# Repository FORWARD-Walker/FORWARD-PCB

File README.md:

MAIN contains ESP-32D Wroom, sensors, and connectors to other boards.
POWER contains voltage regulators and connection for AA battery pack.

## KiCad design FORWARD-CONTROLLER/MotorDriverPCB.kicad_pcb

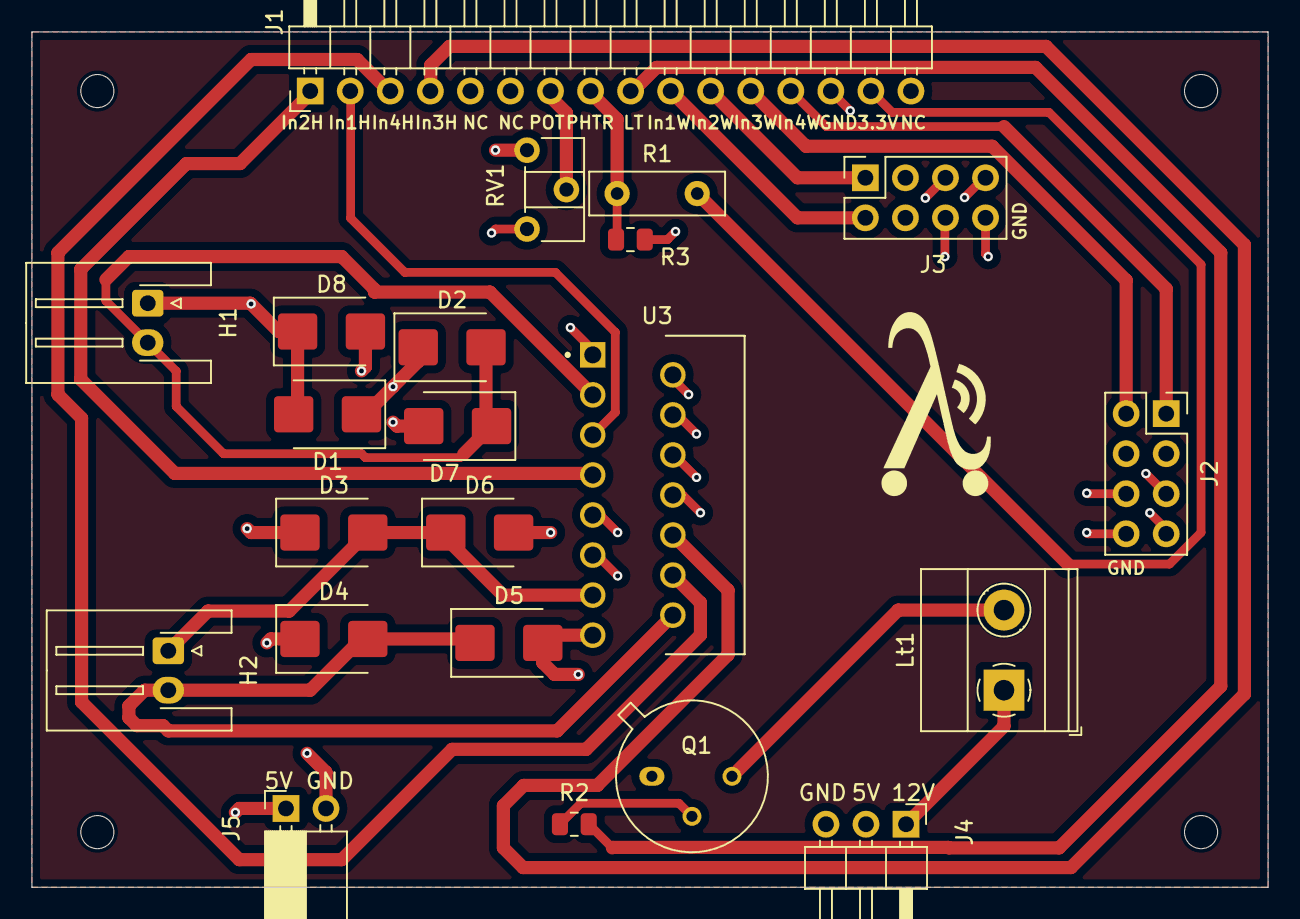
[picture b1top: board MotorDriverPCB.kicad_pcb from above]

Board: 4 copper layers, 78.4 x 54.2 mm, 22 parts (0 on the bottom side), 21 nets.

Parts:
D1, D2, D3, D4, D5, D6, D7, D8: STTH212U; D_SMB
H1, H2: Screw_Terminal_01x02; JST_XH_S2B-XH-A-1_1x02_P2.50mm_Horizontal
J1: Conn_01x16_Pin; PinHeader_1x16_P2.54mm_Horizontal
J2, J3: Conn_02x04_Counter_Clockwise; PinSocket_2x04_P2.54mm_Vertical
J4: Conn_01x03_Socket; PinHeader_1x03_P2.54mm_Horizontal
J5: Conn_01x02_Socket; PinSocket_1x02_P2.54mm_Horizontal
Lt1: Screw_Terminal_01x02; TerminalBlock_Phoenix_MKDS-1,5-2-5.08_1x02_P5.08mm_Horizont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
Q1: 2N2219; TO-39-3
R1: R_Photo; R_Box_L8.4mm_W2.5mm_P5.08mm
R2: 1k; R_0805_2012Metric
R3: 10k; R_0805_2012Metric
RV1: R_Potentiometer; Potentiometer_ACP_CA6-H2,5_Horizontal
U3: L298N; TO127P2020X500X2100-15

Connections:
+3.3V: J1.15, R1.2
+5V: D1.1 (K), D2.1 (K), D3.1 (K), D4.1 (K), J2.5, J2.6, J2.7, J3.5, J3.6, J3.7, J4.2, J5.1, RV1.1, U3.4 (VS), U3.6 (ENA), U3.9 (VSS), U3.11 (ENB)
+12V: J4.1, Lt1.1
GND: D5.2 (A), D6.2 (A), D7.2 (A), D8.2 (A), J1.14, J2.8, J3.8, J4.3, J5.2, Q1.1 (E), R3.2, RV1.3, U3.1 (SENSE_A), U3.8 (GND), U3.15 (SENSE_B)
IN1U2: J1.10, J3.2
IN1U3: J1.2, U3.5 (IN1)
IN2U2: J1.11, J3.1
IN2U3: J1.1, U3.7 (IN2)
IN3U2: J1.12, J2.2
IN3U3: J1.4, U3.10 (IN3)
IN4U2: J1.13, J2.1
IN4U3: J1.3, U3.12 (IN4)
LIGHT: J1.9, R2.2
NPN: Lt1.2, Q1.3 (C)
unnamed: Q1.2 (B), R2.1
OUT1U3: D1.2 (A), D8.1 (K), H1.1, U3.2 (OUT1)
OUT2U3: D2.2 (A), D7.1 (K), H1.2, U3.3 (OUT2)
OUT3U3: D3.2 (A), D6.1 (K), H2.1, U3.13 (OUT3)
OUT4U3: D4.2 (A), D5.1 (K), H2.2, U3.14 (OUT4)
PHOTO: J1.8, R1.1, R3.1
POW: J1.7, RV1.2

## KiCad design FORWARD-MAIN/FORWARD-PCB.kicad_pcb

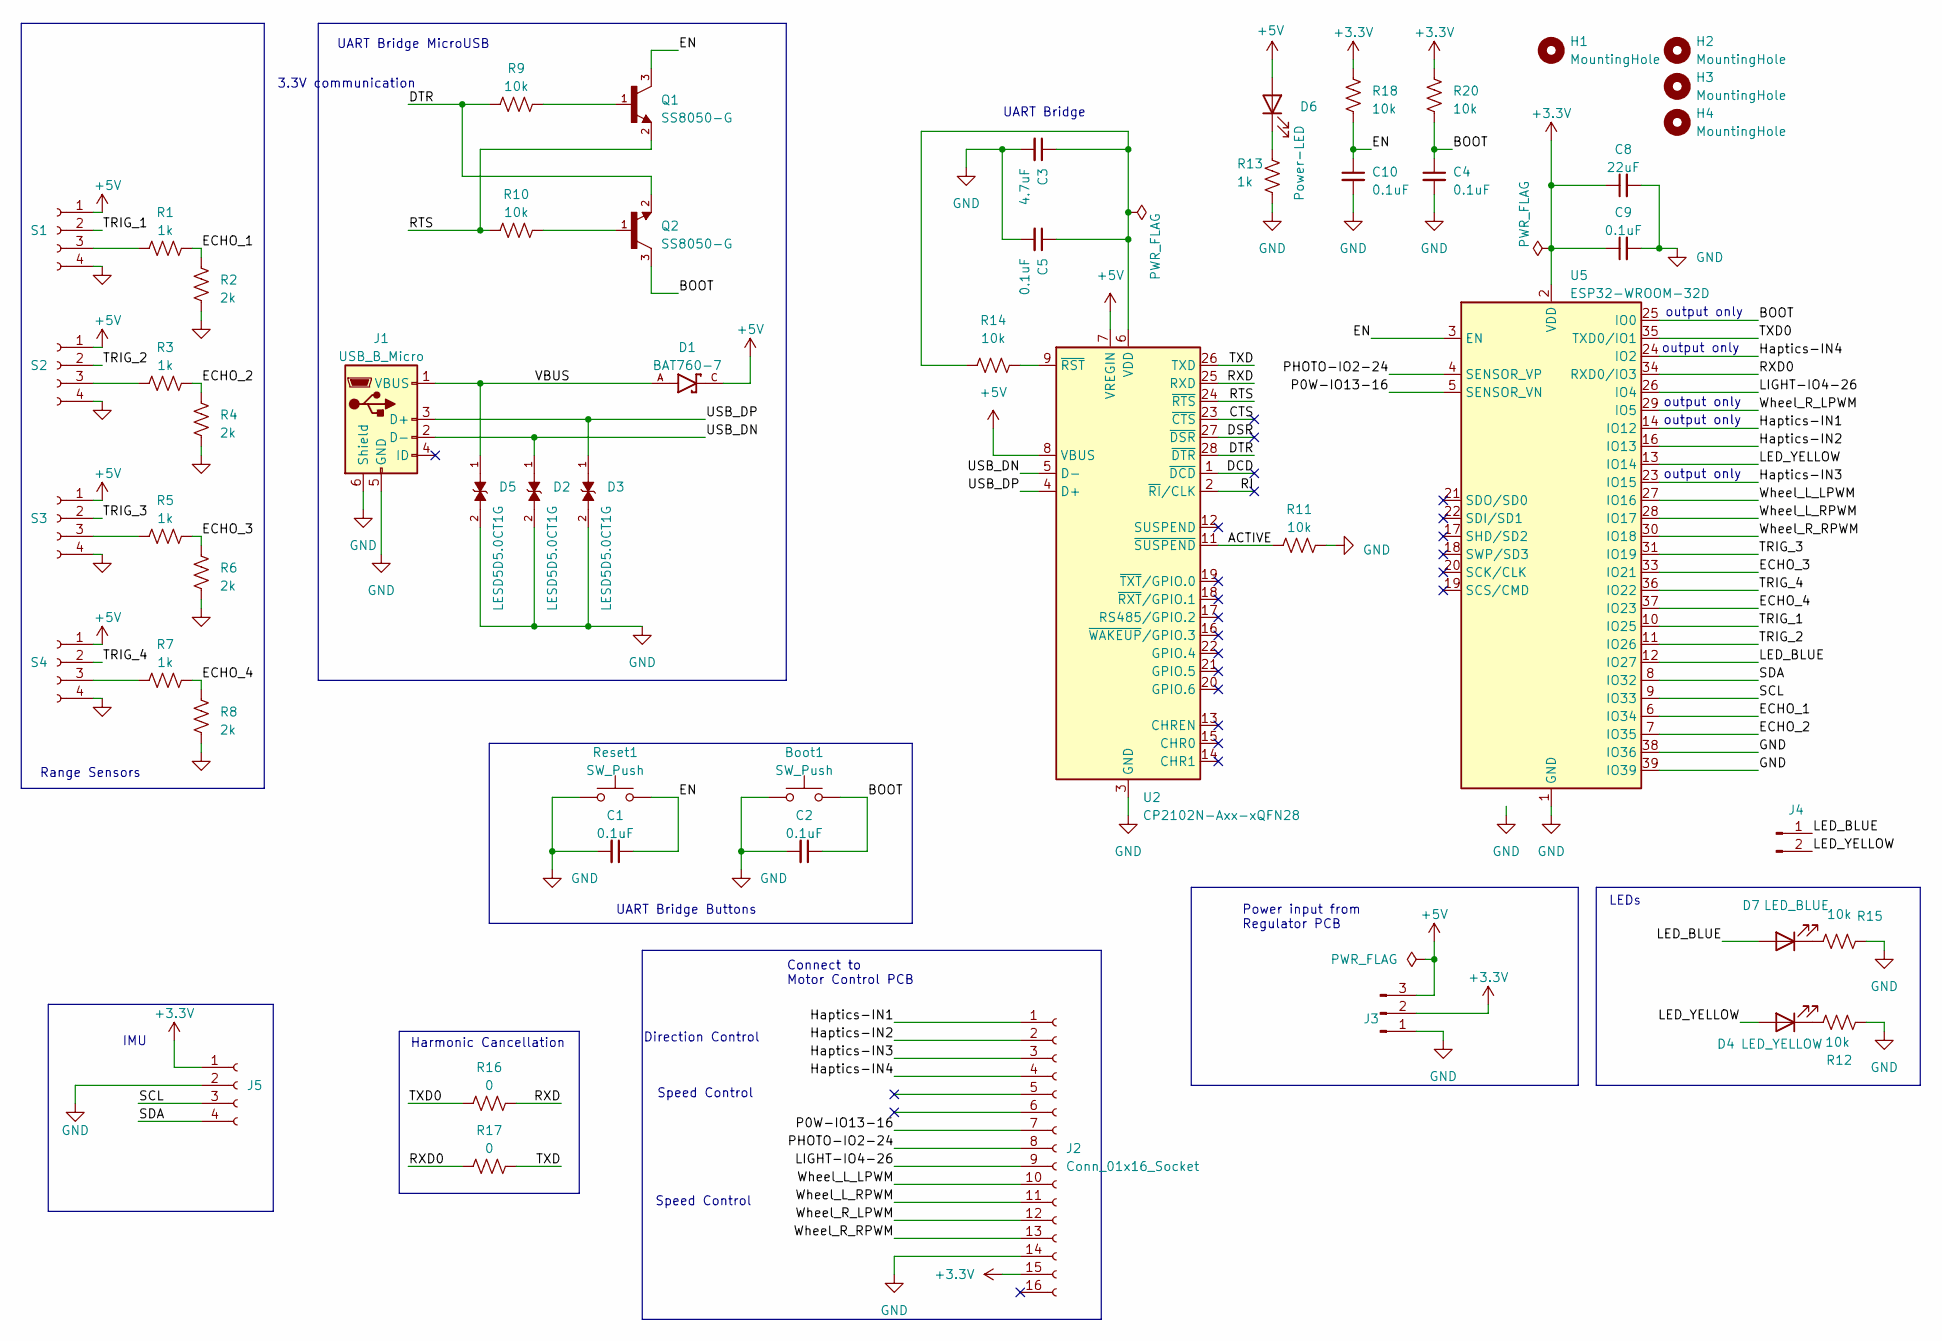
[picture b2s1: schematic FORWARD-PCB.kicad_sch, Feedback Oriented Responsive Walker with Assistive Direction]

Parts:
Boot1: SW_Push; SW_SPST_TL3305A
C1, C2, C4, C5, C9, C10: 0.1uF; C_0805_2012Metric
C3: 4.7uF; C_0805_2012Metric
C8: 22uF; C_0805_2012Metric
D1: BAT760-7; SOD2513X120N; PARTREV 9-2
D2, D3, D5: LESD5D5.0CT1G; TVS_LESD5D5.0CT1G; PARTREV O
D4: LED_YELLOW; LED_0805_2012Metric
D6: Power-LED; LED_0805_2012Metric
D7: LED_BLUE; LED_0805_2012Metric
H1, H2, H3, H4: MountingHole; MountingHole_2.2mm_M2
J1: USB_B_Micro; USB_Micro-B_Wuerth_629105150521
J2: Conn_01x16_Socket; PinSocket_1x16_P2.54mm_Horizontal
J3: Conn_01x03_Pin; JST_XH_S3B-XH-A_1x03_P2.50mm_Horizontal
J4: Conn_01x02_Pin; PinSocket_1x02_P2.54mm_Horizontal
J5: Conn_01x04_Socket; PinSocket_1x04_P2.54mm_Vertical
Q1, Q2: SS8050-G; TRANS_SS8050-G; PARTREV A
R1, R3, R5, R7, R13: 1k; R_0805_2012Metric
R2, R4, R6, R8: 2k; R_0805_2012Metric
R9, R10, R11, R12, R14, R15, R18, R20: 10k; R_0805_2012Metric
R16, R17: 0; R_0805_2012Metric
Reset1: SW_Push; SW_SPST_TL3305A
S1, S2, S3, S4: Conn_01x04_Socket; JST_XH_S4B-XH-A_1x04_P2.50mm_Horizontal
U2: CP2102N-Axx-xQFN28; QFN-28-1EP_5x5mm_P0.5mm_EP3.35x3.35mm
U5: ESP32-WROOM-32D

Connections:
+3.3V: C8.1, C9.1, J2.15, J3.2, J5.1, R18.1, R20.1, U5.2 (VDD)
+5V: D1.C, D6.2 (A), J3.3, S1.1, S2.1, S3.1, S4.1, U2.7 (VREGIN), U2.8 (VBUS)
/ACTIVE: R11.1, U2.11 (~SUSPEND)
/BOOT: Boot1.2, C2.1, C4.1, Q2.3, R20.2, U5.25 (IO0)
/CTS: U2.23 (~CTS)
/DCD: U2.1 (~DCD)
/DSR: U2.27 (~DSR)
/DTR: Q2.2, R9.1, U2.28 (~DTR)
/ECHO_1: R1.2, R2.1, U5.6 (IO34)
/ECHO_2: R3.2, R4.1, U5.7 (IO35)
/ECHO_3: R5.2, R6.1, U5.33 (IO21)
/ECHO_4: R7.2, R8.1, U5.37 (IO23)
/EN: C1.1, C10.1, Q1.3, R18.2, Reset1.2, U5.3 (EN)
/Haptics-IN1: J2.1, U5.14 (IO12)
/Haptics-IN2: J2.2, U5.16 (IO13)
/Haptics-IN3: J2.3, U5.23 (IO15)
/Haptics-IN4: J2.4, U5.24 (IO2)
/LED_BLUE: D7.2 (A), J4.1, U5.12 (IO27)
/LED_YELLOW: D4.2 (A), J4.2, U5.13 (IO14)
/LIGHT-IO4-26: J2.9, U5.26 (IO4)
/P0W-IO13-16: J2.7, U5.5 (SENSOR_VN)
/PHOTO-IO2-24: J2.8, U5.4 (SENSOR_VP)
/RI: U2.2 (~RI/CLK)
/RTS: Q1.2, R10.1, U2.24 (~RTS)
/RXD: R16.2, U2.25 (RXD)
/RXD0: R17.1, U5.34 (RXD0/IO3)
/SCL: J5.3, U5.9 (IO33)
/SDA: J5.4, U5.8 (IO32)
/TRIG_1: S1.2, U5.10 (IO25)
/TRIG_2: S2.2, U5.11 (IO26)
/TRIG_3: S3.2, U5.31 (IO19)
/TRIG_4: S4.2, U5.36 (IO22)
/TXD: R17.2, U2.26 (TXD)
/TXD0: R16.1, U5.35 (TXD0/IO1)
/USB_DN: D2.1, J1.2 (D-), U2.5 (D-)
/USB_DP: D3.1, J1.3 (D+), U2.4 (D+)
/VBUS: D1.A, D5.1, J1.1 (VBUS)
/Wheel_L_LPWM: J2.10, U5.27 (IO16)
/Wheel_L_RPWM: J2.11, U5.28 (IO17)
/Wheel_R_LPWM: J2.12, U5.29 (IO5)
/Wheel_R_RPWM: J2.13, U5.30 (IO18)
GND: Boot1.1, C1.2, C2.2, C3.2, C4.2, C5.2, C8.2, C9.2, C10.2, D2.2, D3.2, D5.2, J1.5 (GND), J1.6 (Shield), J2.14, J3.1, J5.2, R2.2, R4.2, R6.2, R8.2, R11.2, R12.2, R13.2, R15.2, Reset1.1, S1.4, S2.4, S3.4, S4.4, U2.3 (GND), U2.29 (GND), U5.1 (GND), U5.15 (GND), U5.38 (IO36), U5.39 (IO39)
unnamed: D4.1 (K), R12.1
unnamed: D6.1 (K), R13.1
unnamed: D7.1 (K), R15.1
unnamed: Q1.1, R9.2
unnamed: Q2.1, R10.2
unnamed: R1.1, S1.3
unnamed: R3.1, S2.3
unnamed: R5.1, S3.3
unnamed: R7.1, S4.3
unnamed: C3.1, C5.1, R14.2, U2.6 (VDD)
unnamed: R14.1, U2.9 (~RST)

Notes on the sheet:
Range Sensors
LEDs
Power input from Regulator PCB
output only
Speed Control
Harmonic Cancellation
Connect to Motor Control PCB
UART Bridge MicroUSB
UART Bridge Buttons
Direction Control
3.3V communication
IMU
UART Bridge

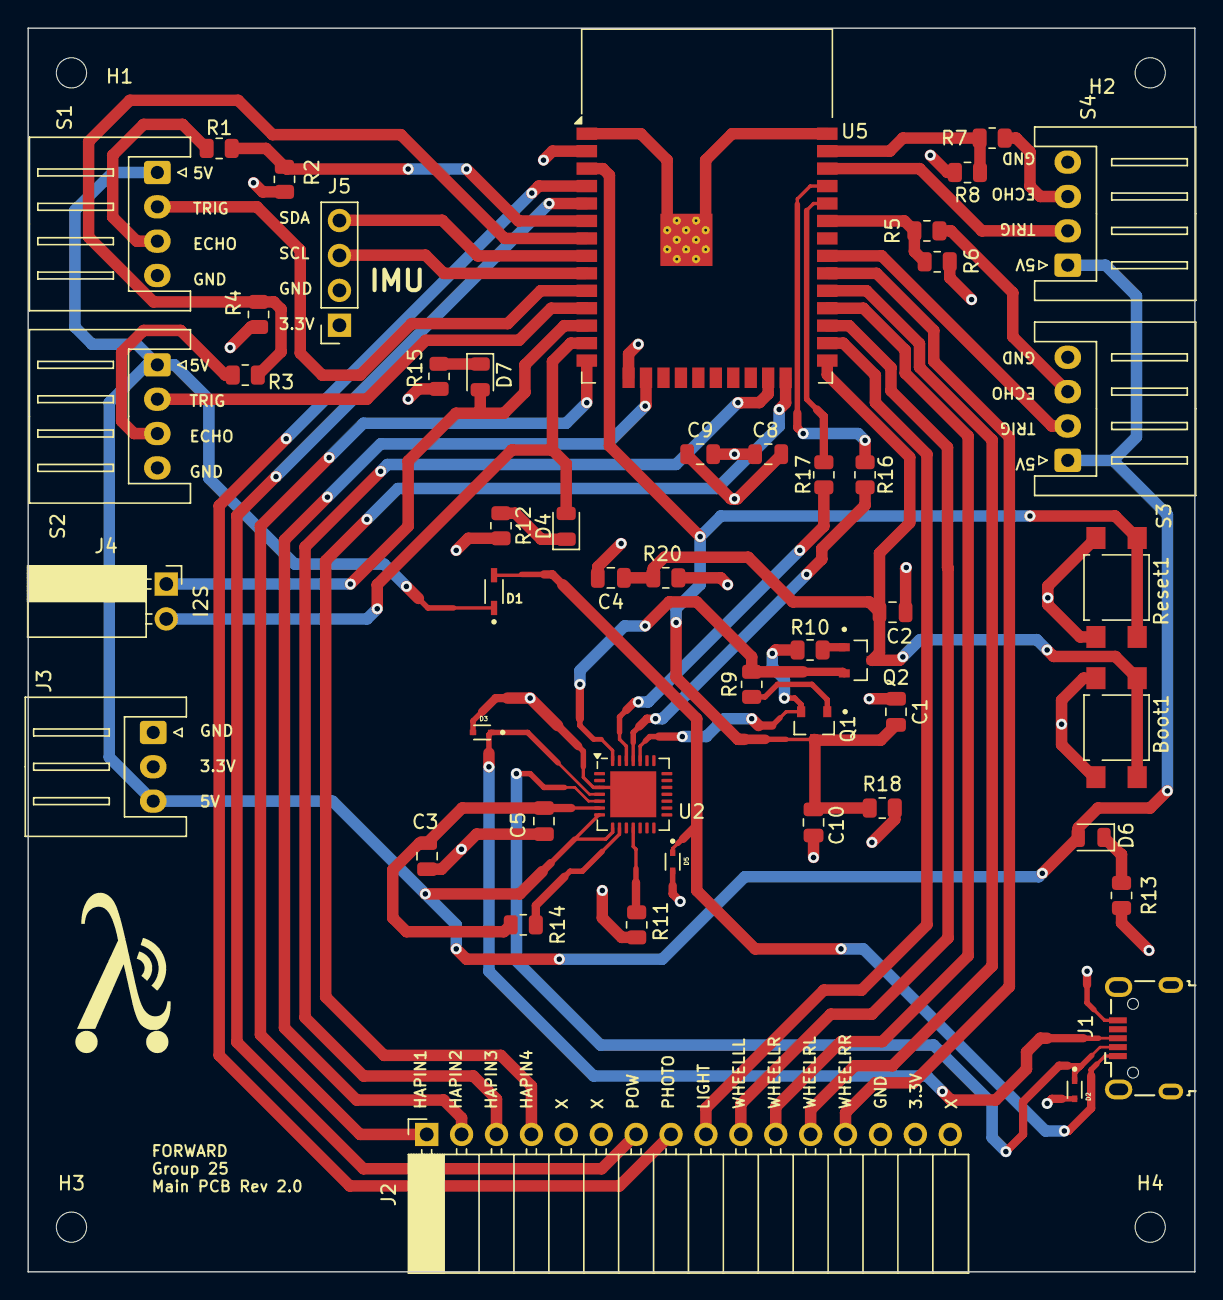
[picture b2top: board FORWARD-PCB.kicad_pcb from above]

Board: 4 copper layers, 84.9 x 90.5 mm, 53 parts (0 on the bottom side), 49 nets.

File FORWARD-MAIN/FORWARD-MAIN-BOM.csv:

"Reference","Value","Datasheet","Footprint","Qty","DNP"
"Boot1,Reset1","SW_Push","~","Button_Switch_SMD:SW_Tactile_SPST_NO_Straight_CK_PTS636Sx25SMTRLFS","2",""
"C1,C2,C4,C5,C9,C10","0.1uF","~","Capacitor_SMD:C_0805_2012Metric","6",""
"C3","4.7uF","~","Capacitor_SMD:C_0805_2012Metric","1",""
"C8","22uF","~","Capacitor_SMD:C_0805_2012Metric","1",""
"D1","BAT760-7","","footprints:SOD2513X120N","1",""
"D2,D3,D5","LESD5D5.0CT1G","","footprints:TVS_LESD5D5.0CT1G","3",""
"D4","LED","~","LED_SMD:LED_0805_2012Metric","1",""
"J1","USB_B_Micro","~","Connector_USB:USB_Micro-B_Molex-105133-0031","1",""
"J3","Conn_01x13_Socket","~","Connector_Phoenix_MC:PhoenixContact_MC_1,5_13-G-3.81_1x13_P3.81mm_Horizontal","1",""
"J4","Conn_01x08_Socket","~","Connector_PinSocket_2.54mm:PinSocket_1x08_P2.54mm_Vertical","1",""
"J5","Screw_Terminal_01x03","~","TerminalBlock_Phoenix:TerminalBlock_Phoenix_MPT-0,5-3-2.54_1x03_P2.54mm_Horizontal","1",""
"L1","Conn_01x06_Socket","~","Connector_JST:JST_EH_S6B-EH_1x06_P2.50mm_Horizontal","1",""
"Q1,Q2","SS8050-G","","footprints:TRANS_SS8050-G","2",""
"R1,R3,R5,R7","1k","~","Resistor_SMD:R_0805_2012Metric","4",""
"R2,R4,R6,R8,R14","2k","~","Resistor_SMD:R_0805_2012Metric","5",""
"R9,R10,R11,R18,R20","10k","~","Resistor_SMD:R_0805_2012Metric","5",""
"R12","22.1k","~","Resistor_SMD:R_0805_2012Metric","1",""
"R13","47.5k","~","Resistor_SMD:R_0805_2012Metric","1",""
"R15,R19","3.2k","~","Resistor_SMD:R_0805_2012Metric","2",""
"R16,R17","0","~","Resistor_SMD:R_0805_2012Metric","2",""
"S1,S2,S3,S4","Conn_01x04_Socket","~","Connector_JST:JST_EH_S4B-EH_1x04_P2.50mm_Horizontal","4",""
"TP4","TestPoint","~","TestPoint:TestPoint_Pad_1.0x1.0mm","1",""
"U2","CP2102N-Axx-xQFN28","https://www.silabs.com/documents/public/data-sheets/cp2102n-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","Package_DFN_QFN:QFN-28-1EP_5x5mm_P0.5mm_EP3.35x3.35mm","1",""
"U5","ESP32-WROOM-32D","https://www.espressif.com/sites/default/files/documentation/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","RF_Module:ESP32-WROOM-32D","1",""

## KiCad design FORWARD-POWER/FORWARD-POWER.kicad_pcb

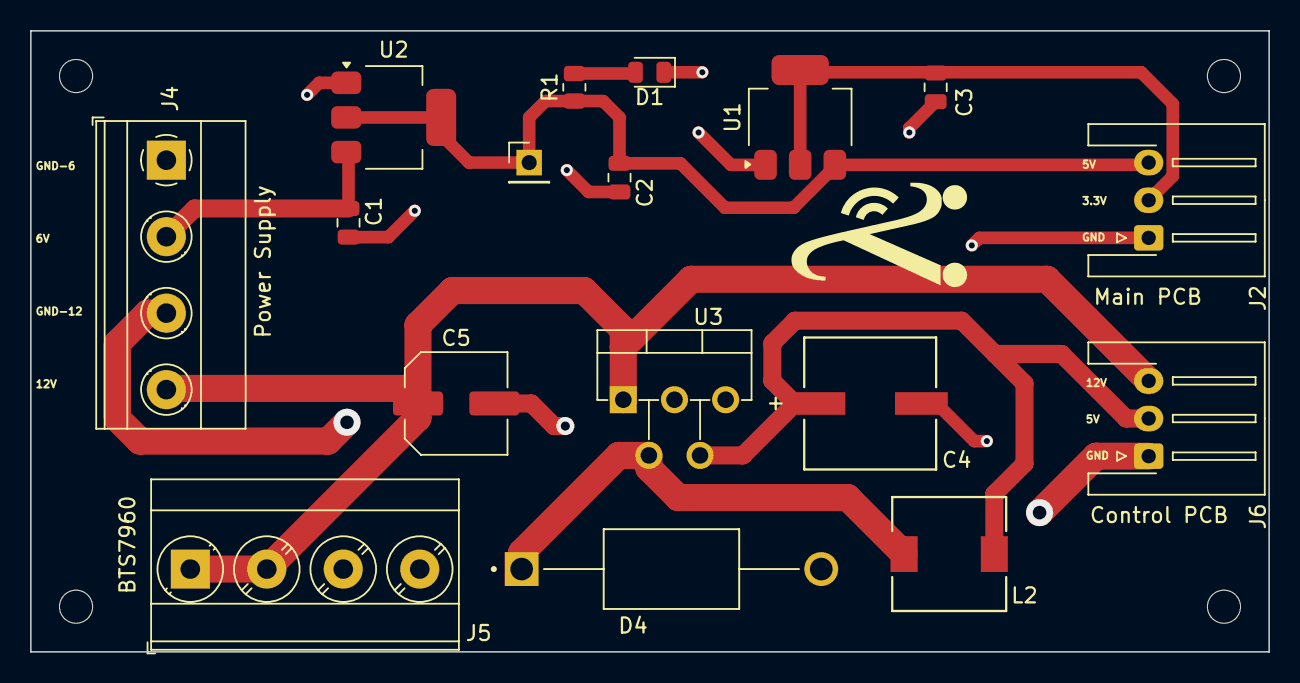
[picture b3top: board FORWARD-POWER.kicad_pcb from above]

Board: 2 copper layers, 82.2 x 41.2 mm, 21 parts (0 on the bottom side), 9 nets.

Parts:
C1: 47uF; C_0805_2012Metric
C2, C3: 22uF; C_0805_2012Metric
C4: UWT1E331MNL1GS; PCAP_8x10-ELECT_NCA
C5: 100uF; C_Elec_6.3x7.7
D1: LED; LED_0805_2012Metric
D4: 1N5822; DIOAD1990W125L900D530
H1, H2, H3, H4: MountingHole; MountingHole_2.2mm_M2
J2, J6: Conn_01x03_Pin; JST_XH_S3B-XH-A-1_1x03_P2.50mm_Horizontal
J3: Conn_01x01_Pin; PinHeader_1x01_P2.54mm_Vertical
J4: Screw_Terminal_01x04; TerminalBlock_Phoenix_MKDS-1,5-4-5.08_1x04_P5.08mm_Horizont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
J5: Screw_Terminal_01x04; TerminalBlock_Phoenix_MKDS-3-4-5.08_1x04_P5.08mm_Horizontal
L2: SRR7045-331M; IND_BOURNS_SRR7045
R1: 2k; R_0805_2012Metric
U1: AMS1117-3.3; SOT-223-3_TabPin2
U2: AMS1117-5.0; SOT-223-3_TabPin2
U3: LM2576-5.0WT; TO-220-5_P3.4x3.7mm_StaggerEven_Lead3.8mm_Vertical

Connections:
+3.3V: C3.1, J2.2, U1.2 (VO)
+5V: C4.1, J6.2, L2.2, U3.4 (FEEDBACK)
+6V: C1.1, J4.2, U2.3 (VI)
+12V: C5.1, J4.4, J5.1, J5.2, J6.3, U3.1 (VIN)
/anet: C2.1, J2.3, J3.1, R1.1, U1.3 (VI), U2.2 (VO)
GND: C1.2, C2.2, C3.2, D1.1 (K), J2.1, J4.1, U1.1 (GND), U2.1 (GND)
GND3: C4.2, C5.2, D4.A, J4.3, J5.3, J5.4, J6.1, U3.3 (GROUND), U3.5 (*ON/OFF)
unnamed: D1.2 (A), R1.2
unnamed: D4.C, L2.1, U3.2 (OUTPUT)

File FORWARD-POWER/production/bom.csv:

Designator,Footprint,Quantity,Value,LCSC Part #
C1,0805,1,47uF,
"C2, C3",0805,2,22uF,
C4,PCAP_8x10-ELECT_NCA,1,UWT1E331MNL1GS,
C5,C_Elec_6.3x7.7,1,100uF,
D1,0805,1,LED,
D4,DIOAD1990W125L900D530,1,1N5822,
"J2, J6",JST_XH_S3B-XH-A-1_1x03_P2.50mm_Horizontal,2,Conn_01x03_Pin,
J3,PinHeader_1x01_P2.54mm_Vertical,1,Conn_01x01_Pin,
J4,"TerminalBlock_Phoenix_MKDS-1,5-4-5.08_1x04_P5.08mm_Horizontal",1,Screw_Terminal_01x04,
J5,TerminalBlock_Phoenix_MKDS-3-4-5.08_1x04_P5.08mm_Horizontal,1,Screw_Terminal_01x04,
L2,IND_BOURNS_SRR7045,1,SRR7045-331M,
R1,0805,1,2k,
U1,SOT-223-3_TabPin2,1,AMS1117-3.3,
U2,SOT-223-3_TabPin2,1,AMS1117-5.0,
U3,TO-220-5_P3.4x3.7mm_StaggerEven_Lead3.8mm_Vertical,1,LM2576-5.0WT,

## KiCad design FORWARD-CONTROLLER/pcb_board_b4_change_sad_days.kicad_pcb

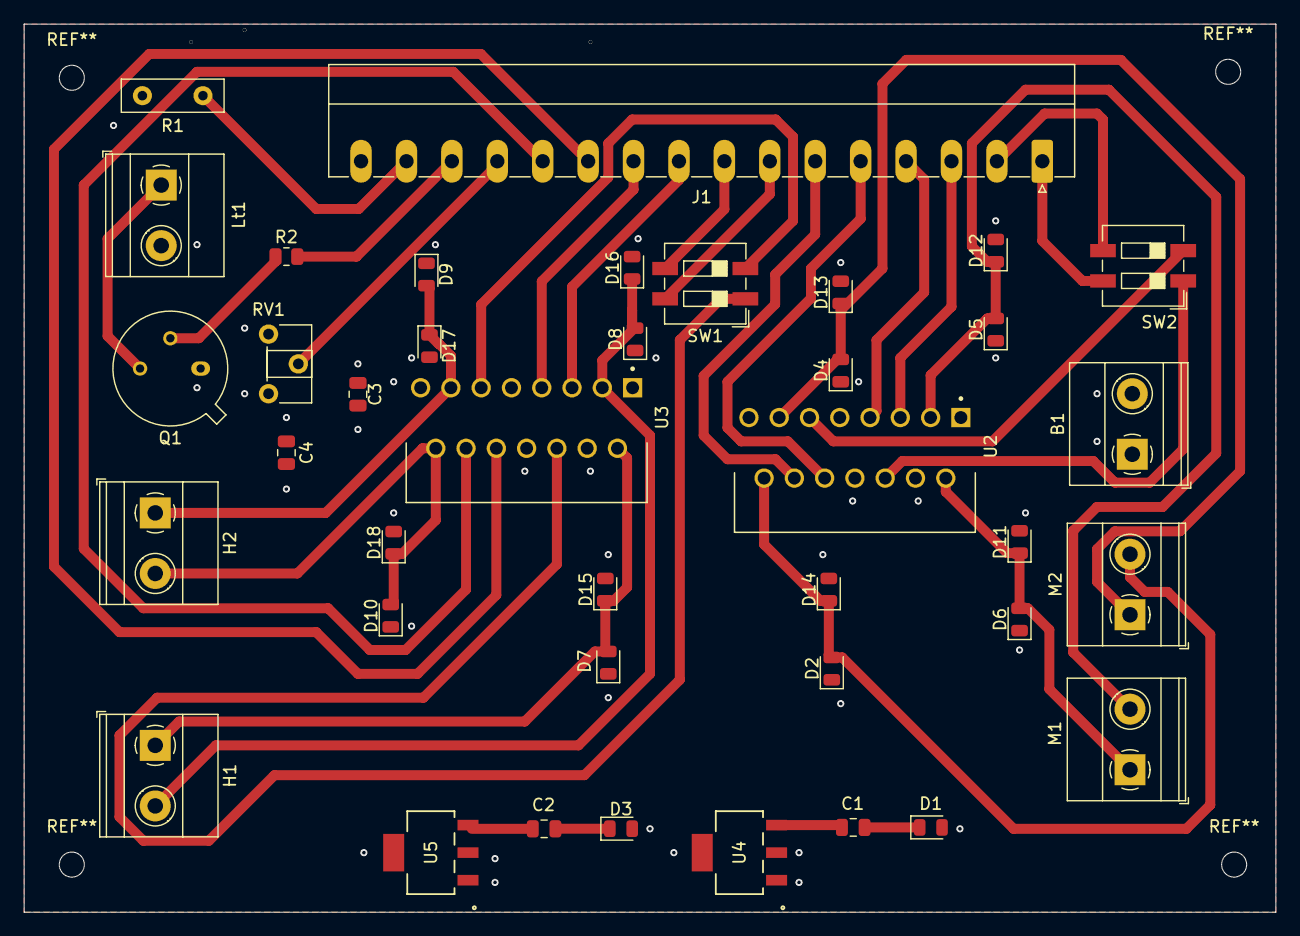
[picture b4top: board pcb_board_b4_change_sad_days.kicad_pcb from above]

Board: 2 copper layers, 105.0 x 74.5 mm, 39 parts (0 on the bottom side), 35 nets.

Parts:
B1: Screw_Terminal_01x02; TerminalBlock_Phoenix_MKDS-1,5-2-5.08_1x02_P5.08mm_Horizont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
C1, C2, C3, C4: 220uF; C_0805_2012Metric
D1, D3: LD271; LED_0805_2012Metric
D2, D4, D5, D6, D7, D8, D9, D10, D11, D12, D13, D14, D15, D16, D17, D18: 1N4002; D_0805_2012Metric
H1, H2: Screw_Terminal_01x02; TerminalBlock_Phoenix_MKDS-1,5-2-5.08_1x02_P5.08mm_Horizont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
J1: Conn_01x16_Pin; PhoenixContact_MC_1,5_16-G-3.81_1x16_P3.81mm_Horizontal
Lt1: Screw_Terminal_01x02; TerminalBlock_Phoenix_MKDS-1,5-2-5.08_1x02_P5.08mm_Horizont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
M1, M2: Screw_Terminal_01x02; TerminalBlock_Phoenix_MKDS-1,5-2-5.08_1x02_P5.08mm_Horizont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
Q1: 2N2219; TO-39-3
R1: R_Photo; R_Box_L8.4mm_W2.5mm_P5.08mm
R2: 1k; R_0805_2012Metric
RV1: R_Potentiometer; Potentiometer_ACP_CA6-H2,5_Horizontal
SW1, SW2: SW_DIP_x02; SW_DIP_SPSTx02_Slide_6.7x6.64mm_W6.73mm_P2.54mm_LowProfile_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
U2, U3: L298N; TO127P2020X500X2100-15
U4, U5: LM7805MPX/NOPB; DCY4_TEX

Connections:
0: C3.2, C4.2, D11.2 (A), D12.2 (A), D13.2 (A), D14.2 (A), D15.2 (A), D16.2 (A), D17.2 (A), D18.2 (A), U3.1 (SENSE_A), U3.8 (GND), U3.15 (SENSE_B), U4.4 (GND), U5.2 (GND), U5.4 (GND)
5V: C1.2, C2.2, C3.1, C4.1, D1.1 (K), D2.1 (K), D3.1 (K), D4.1 (K), D5.1 (K), D6.1 (K), D7.1 (K), D8.1 (K), D9.1 (K), D10.1 (K), J1.16, RV1.1, U2.4 (VS), U3.4 (VS)
12V: B1.1, U2.9 (VSS), U3.9 (VSS), U4.1 (INPUT), U5.1 (INPUT)
ENAU2: SW2.1, U2.6 (ENA)
ENAU3: SW1.1, U3.6 (ENA)
ENBU2: SW2.2, U2.11 (ENB)
ENBU3: SW1.2, U3.11 (ENB)
GND: B1.2, Lt1.2, Q1.1 (E), R1.2, RV1.3, U2.1 (SENSE_A), U2.8 (GND), U2.15 (SENSE_B), U4.2 (GND)
IN1U2: J1.3, U2.5 (IN1)
IN1U3: J1.9, U3.5 (IN1)
IN2U2: J1.4, U2.7 (IN2)
IN2U3: J1.10, U3.7 (IN2)
IN3U2: J1.5, U2.10 (IN3)
IN3U3: J1.11, U3.10 (IN3)
IN4U2: J1.6, U2.12 (IN4)
IN4U3: J1.12, U3.12 (IN4)
LIGHT: J1.14, R2.2
NPN: Lt1.1, Q1.3 (C)
unnamed: C1.1, D1.2 (A), U4.3 (OUTPUT)
unnamed: C2.1, D3.2 (A), U5.3 (OUTPUT)
unnamed: Q1.2 (B), R2.1
OUT1U2: D6.2 (A), D11.1 (K), M1.1, U2.2 (OUT1)
OUT1U3: D7.2 (A), D15.1 (K), H1.1, U3.2 (OUT1)
OUT2U2: D5.2 (A), D12.1 (K), M1.2, U2.3 (OUT2)
OUT2U3: D8.2 (A), D16.1 (K), H1.2, U3.3 (OUT2)
OUT3U2: D4.2 (A), D13.1 (K), M2.1, U2.13 (OUT3)
OUT3U3: D9.2 (A), D17.1 (K), H2.1, U3.13 (OUT3)
OUT4U2: D2.2 (A), D14.1 (K), M2.2, U2.14 (OUT4)
OUT4U3: D10.2 (A), D18.1 (K), H2.2, U3.14 (OUT4)
PHOTO: J1.15, R1.1
POW: J1.13, RV1.2
SW1U2: J1.1, SW2.4
SW1U3: J1.7, SW1.4
SW2U2: J1.2, SW2.3
SW2U3: J1.8, SW1.3

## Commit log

2025-01-21 power, main, dependencies
2025-01-21 minor tweaks
2025-01-21 tutorials, esp uart bridge sch
2025-01-21 autorouting trying but failing
2025-01-22 routing progress
2025-01-23 Redesign of pcb
2025-01-24 itried
2025-01-25 a good iteration!
2025-01-25 regulator pcb done
2025-01-31 ready to order (i think)
2025-01-31 stuffs
2025-02-05 PCB order rev 1.0
2025-02-06 morgan controller board
2025-02-08 MAIN PCB rev 2.0
2025-02-08 REGULATOR PCB rev 2.0
2025-02-15 backups
2025-02-25 fix i2c but still an issue
2025-02-28 most recent iter
2025-02-28 transfer to pc
2025-03-03 newest
2025-03-06 finalized i2c on 3233
2025-03-06 re-routing rev 2.0
2025-03-25 rev 2.0 PCB official
2025-04-11 PCB Revision 2.0
2025-04-11 the real motor rev 2.0
